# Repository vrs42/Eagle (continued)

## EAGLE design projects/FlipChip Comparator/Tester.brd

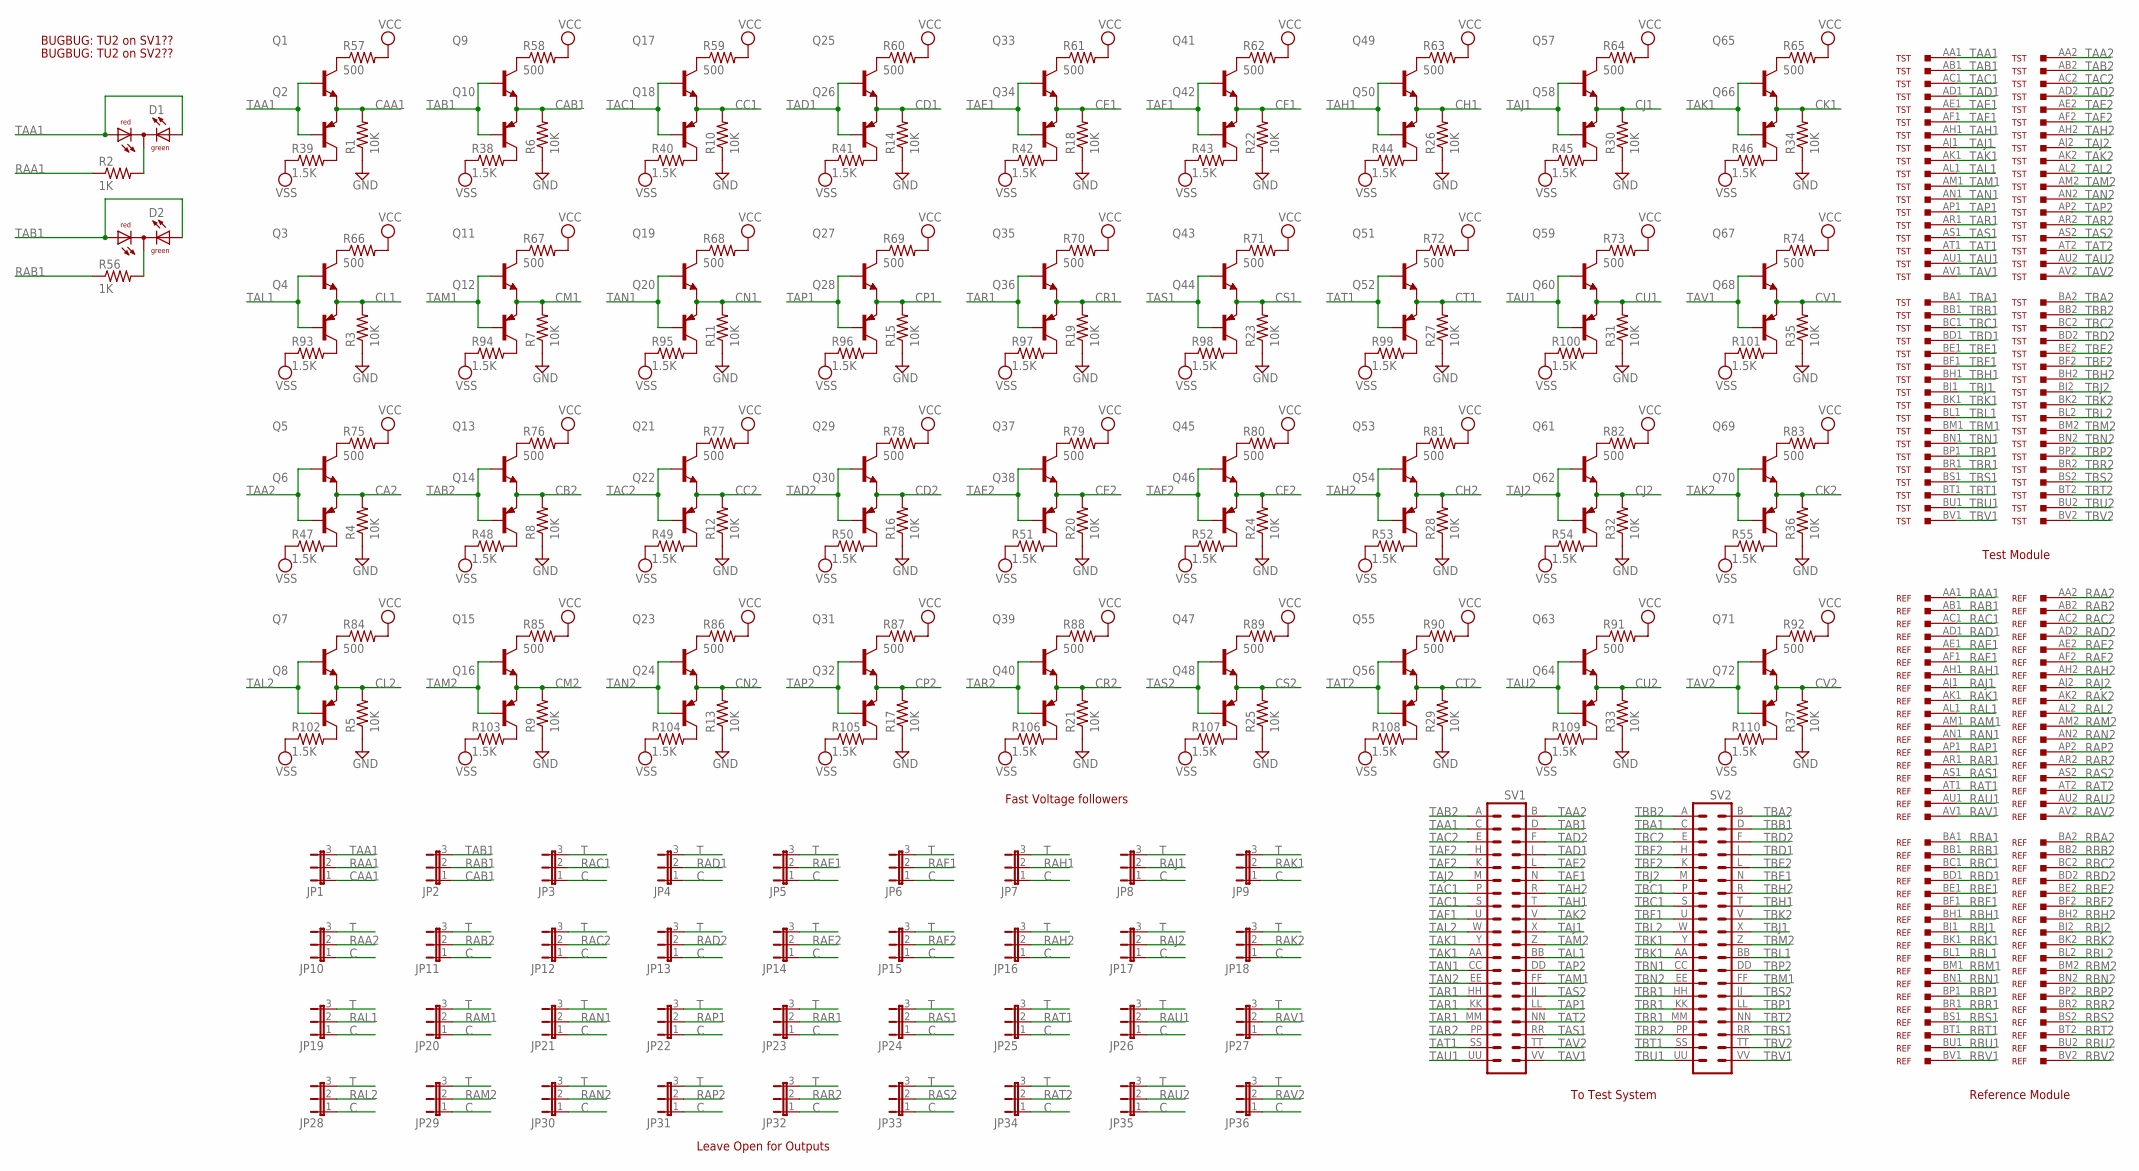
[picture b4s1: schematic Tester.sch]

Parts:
D1, D2: DUOLED5MM
JP1, JP2, JP3, JP4, JP5, JP6, JP7, JP8, JP9, JP10, JP11, JP12, JP13, JP14, JP15, JP16, JP17, JP18, JP19, JP20, JP21, JP22, JP23, JP24, JP25, JP26, JP27, JP28, JP29, JP30, JP31, JP32, JP33, JP34, JP35, JP36: JP2E; JP2
Q1, Q3, Q5, Q7, Q9, Q11, Q13, Q15, Q17, Q19, Q21, Q23, Q25, Q27, Q29, Q31, Q33, Q35, Q37, Q39, Q41, Q43, Q45, Q47, Q49, Q51, Q53, Q55, Q57, Q59, Q61, Q63, Q65, Q67, Q69, Q71: -NPN-TO5; TO5
Q2, Q4, Q6, Q8, Q10, Q12, Q14, Q16, Q18, Q20, Q22, Q24, Q26, Q28, Q30, Q32, Q34, Q36, Q38, Q40, Q42, Q44, Q46, Q48, Q50, Q52, Q54, Q56, Q58, Q60, Q62, Q64, Q66, Q68, Q70, Q72: -PNP-TO5; TO5
R1, R3, R4, R5, R6, R7, R8, R9, R10, R11, R12, R13, R14, R15, R16, R17, R18, R19, R20, R21, R22, R23, R24, R25, R26, R27, R28, R29, R30, R31, R32, R33, R34, R35, R36, R37: 10K; 0207/10
R2, R56: 1K; 0207/10
R38, R39, R40, R41, R42, R43, R44, R45, R46, R47, R48, R49, R50, R51, R52, R53, R54, R55, R93, R94, R95, R96, R97, R98, R99, R100, R101, R102, R103, R104, R105, R106, R107, R108, R109, R110: 1.5K; 0207/10
R57, R58, R59, R60, R61, R62, R63, R64, R65, R66, R67, R68, R69, R70, R71, R72, R73, R74, R75, R76, R77, R78, R79, R80, R81, R82, R83, R84, R85, R86, R87, R88, R89, R90, R91, R92: 500; 0207/10
REF: W971; H807-2
SV1, SV2: DEC40PINV
TST: W971; H807-2

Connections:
C: JP3.1, JP4.1, JP5.1, JP6.1, JP7.1, JP8.1, JP9.1, JP10.1, JP11.1, JP12.1, JP13.1, JP14.1, JP15.1, JP16.1, JP17.1, JP18.1, JP19.1, JP20.1, JP21.1, JP22.1, JP23.1, JP24.1, JP25.1, JP26.1, JP27.1, JP28.1, JP29.1, JP30.1, JP31.1, JP32.1, JP33.1, JP34.1, JP35.1, JP36.1
CA2: Q5.1 (E), Q6.1 (E), R4.2
CAA1: JP1.1, Q1.1 (E), Q2.1 (E), R1.2
CAB1: JP2.1, Q9.1 (E), Q10.1 (E), R6.2
CB2: Q13.1 (E), Q14.1 (E), R8.2
CC1: Q17.1 (E), Q18.1 (E), R10.2
CC2: Q21.1 (E), Q22.1 (E), R12.2
CD1: Q25.1 (E), Q26.1 (E), R14.2
CD2: Q29.1 (E), Q30.1 (E), R16.2
CE1: Q33.1 (E), Q34.1 (E), R18.2
CE2: Q37.1 (E), Q38.1 (E), R20.2
CF1: Q41.1 (E), Q42.1 (E), R22.2
CF2: Q45.1 (E), Q46.1 (E), R24.2
CH1: Q49.1 (E), Q50.1 (E), R26.2
CH2: Q53.1 (E), Q54.1 (E), R28.2
CJ1: Q57.1 (E), Q58.1 (E), R30.2
CJ2: Q61.1 (E), Q62.1 (E), R32.2
CK1: Q65.1 (E), Q66.1 (E), R34.2
CK2: Q69.1 (E), Q70.1 (E), R36.2
CL1: Q3.1 (E), Q4.1 (E), R3.2
CL2: Q7.1 (E), Q8.1 (E), R5.2
CM1: Q11.1 (E), Q12.1 (E), R7.2
CM2: Q15.1 (E), Q16.1 (E), R9.2
CN1: Q19.1 (E), Q20.1 (E), R11.2
CN2: Q23.1 (E), Q24.1 (E), R13.2
CP1: Q27.1 (E), Q28.1 (E), R15.2
CP2: Q31.1 (E), Q32.1 (E), R17.2
CR1: Q35.1 (E), Q36.1 (E), R19.2
CR2: Q39.1 (E), Q40.1 (E), R21.2
CS1: Q43.1 (E), Q44.1 (E), R23.2
CS2: Q47.1 (E), Q48.1 (E), R25.2
CT1: Q51.1 (E), Q52.1 (E), R27.2
CT2: Q55.1 (E), Q56.1 (E), R29.2
CU1: Q59.1 (E), Q60.1 (E), R31.2
CU2: Q63.1 (E), Q64.1 (E), R33.2
CV1: Q67.1 (E), Q68.1 (E), R35.2
CV2: Q71.1 (E), Q72.1 (E), R37.2
GND: R1.1, R3.1, R4.1, R5.1, R6.1, R7.1, R8.1, R9.1, R10.1, R11.1, R12.1, R13.1, R14.1, R15.1, R16.1, R17.1, R18.1, R19.1, R20.1, R21.1, R22.1, R23.1, R24.1, R25.1, R26.1, R27.1, R28.1, R29.1, R30.1, R31.1, R32.1, R33.1, R34.1, R35.1, R36.1, R37.1
unnamed: D1.K (C), R2.2
unnamed: Q2.3 (C), R39.2
unnamed: Q1.3 (C), R57.1
unnamed: Q9.3 (C), R58.1
unnamed: Q17.3 (C), R59.1
unnamed: Q25.3 (C), R60.1
unnamed: Q33.3 (C), R61.1
unnamed: Q41.3 (C), R62.1
unnamed: Q49.3 (C), R63.1
unnamed: Q57.3 (C), R64.1
unnamed: Q65.3 (C), R65.1
unnamed: Q10.3 (C), R38.2
unnamed: Q18.3 (C), R40.2
unnamed: Q26.3 (C), R41.2
unnamed: Q34.3 (C), R42.2
unnamed: Q42.3 (C), R43.2
unnamed: Q50.3 (C), R44.2
unnamed: Q58.3 (C), R45.2
unnamed: Q66.3 (C), R46.2
unnamed: Q6.3 (C), R47.2
unnamed: Q4.3 (C), R93.2
unnamed: Q12.3 (C), R94.2
unnamed: Q14.3 (C), R48.2
unnamed: Q22.3 (C), R49.2
unnamed: Q20.3 (C), R95.2
unnamed: Q28.3 (C), R96.2
unnamed: Q30.3 (C), R50.2
unnamed: Q38.3 (C), R51.2
unnamed: Q36.3 (C), R97.2
unnamed: Q44.3 (C), R98.2
unnamed: Q46.3 (C), R52.2
unnamed: Q54.3 (C), R53.2
unnamed: Q52.3 (C), R99.2
unnamed: Q60.3 (C), R100.2
unnamed: Q62.3 (C), R54.2
unnamed: Q70.3 (C), R55.2
unnamed: Q68.3 (C), R101.2
unnamed: D2.K (C), R56.2
unnamed: Q8.3 (C), R102.2
unnamed: Q16.3 (C), R103.2
unnamed: Q24.3 (C), R104.2
unnamed: Q32.3 (C), R105.2
unnamed: Q40.3 (C), R106.2
unnamed: Q48.3 (C), R107.2
unnamed: Q56.3 (C), R108.2
unnamed: Q64.3 (C), R109.2
unnamed: Q72.3 (C), R110.2
unnamed: Q3.3 (C), R66.1
unnamed: Q11.3 (C), R67.1
unnamed: Q19.3 (C), R68.1
unnamed: Q27.3 (C), R69.1
unnamed: Q35.3 (C), R70.1
unnamed: Q43.3 (C), R71.1
unnamed: Q51.3 (C), R72.1
unnamed: Q59.3 (C), R73.1
unnamed: Q67.3 (C), R74.1
unnamed: Q5.3 (C), R75.1
unnamed: Q13.3 (C), R76.1
unnamed: Q21.3 (C), R77.1
unnamed: Q29.3 (C), R78.1
unnamed: Q37.3 (C), R79.1
unnamed: Q45.3 (C), R80.1
unnamed: Q53.3 (C), R81.1
unnamed: Q61.3 (C), R82.1
unnamed: Q69.3 (C), R83.1
unnamed: Q7.3 (C), R84.1
unnamed: Q15.3 (C), R85.1
unnamed: Q23.3 (C), R86.1
unnamed: Q31.3 (C), R87.1
unnamed: Q39.3 (C), R88.1
unnamed: Q47.3 (C), R89.1
unnamed: Q55.3 (C), R90.1
unnamed: Q63.3 (C), R91.1
unnamed: Q71.3 (C), R92.1
RAA1: JP1.2, R2.1, REF.AA1
RAA2: JP10.2, REF.AA2
RAB1: JP2.2, R56.1, REF.AB1
RAB2: JP11.2, REF.AB2
RAC1: JP3.2, REF.AC1
RAC2: JP12.2, REF.AC2
RAD1: JP4.2, REF.AD1
RAD2: JP13.2, REF.AD2
RAE1: JP5.2, REF.AE1
RAE2: JP14.2, REF.AE2
RAF1: JP6.2, REF.AF1
RAF2: JP15.2, REF.AF2
RAH1: JP7.2, REF.AH1
RAH2: JP16.2, REF.AH2
RAJ1: JP8.2, REF.AJ1
RAJ2: JP17.2, REF.AJ2
RAK1: JP9.2, REF.AK1
RAK2: JP18.2, REF.AK2
RAL1: JP19.2, REF.AL1
RAL2: JP28.2, REF.AL2
RAM1: JP20.2, REF.AM1
RAM2: JP29.2, REF.AM2
RAN1: JP21.2, REF.AN1
RAN2: JP30.2, REF.AN2
RAP1: JP22.2, REF.AP1
RAP2: JP31.2, REF.AP2
RAR1: JP23.2, REF.AR1
RAR2: JP32.2, REF.AR2
RAS1: JP24.2, REF.AS1
RAS2: JP33.2, REF.AS2
RAT1: JP25.2, REF.AT1
RAT2: JP34.2, REF.AT2
RAU1: JP26.2, REF.AU1
RAU2: JP35.2, REF.AU2
RAV1: JP27.2, REF.AV1
RAV2: JP36.2, REF.AV2
RBA1: REF.BA1
RBA2: REF.BA2
RBB1: REF.BB1
RBB2: REF.BB2
RBC1: REF.BC1
RBC2: REF.BC2
RBD1: REF.BD1
RBD2: REF.BD2
RBE1: REF.BE1
RBE2: REF.BE2
RBF1: REF.BF1
RBF2: REF.BF2
RBH1: REF.BH1
RBH2: REF.BH2
RBJ1: REF.BJ1
RBJ2: REF.BJ2
RBK1: REF.BK1
RBK2: REF.BK2
RBL1: REF.BL1
RBL2: REF.BL2
RBM1: REF.BM1
RBM2: REF.BM2
RBN1: REF.BN1
RBN2: REF.BN2
RBP1: REF.BP1
RBP2: REF.BP2
RBR1: REF.BR1
RBR2: REF.BR2
RBS1: REF.BS1
RBS2: REF.BS2
RBT1: REF.BT1
RBT2: REF.BT2
RBU1: REF.BU1
RBU2: REF.BU2
RBV1: REF.BV1
RBV2: REF.BV2
T: JP3.3, JP4.3, JP5.3, JP6.3, JP7.3, JP8.3, JP9.3, JP10.3, JP11.3, JP12.3, JP13.3, JP14.3, JP15.3, JP16.3, JP17.3, JP18.3, JP19.3, JP20.3, JP21.3, JP22.3, JP23.3, JP24.3, JP25.3, JP26.3, JP27.3, JP28.3, JP29.3, JP30.3, JP31.3, JP32.3, JP33.3, JP34.3, JP35.3, JP36.3
TAA1: D1.AG, D1.AR, JP1.3, Q1.2 (B), Q2.2 (B), SV1.C (3), TST.AA1
TAA2: Q5.2 (B), Q6.2 (B), SV1.B (2), TST.AA2
TAB1: D2.AG, D2.AR, JP2.3, Q9.2 (B), Q10.2 (B), SV1.D (4), TST.AB1
TAB2: Q13.2 (B), Q14.2 (B), SV1.A (1), TST.AB2
TAC1: Q17.2 (B), Q18.2 (B), SV1.P (13), SV1.S (15), TST.AC1
TAC2: Q21.2 (B), Q22.2 (B), SV1.E (5), TST.AC2
TAD1: Q25.2 (B), Q26.2 (B), SV1.J (8), TST.AD1
TAD2: Q29.2 (B), Q30.2 (B), SV1.F (6), TST.AD2
TAE1: Q33.2 (B), Q34.2 (B), SV1.N (12), TST.AE1
TAE2: Q37.2 (B), Q38.2 (B), SV1.L (10), TST.AE2
TAF1: Q41.2 (B), Q42.2 (B), SV1.U (17), TST.AF1
TAF2: Q45.2 (B), Q46.2 (B), SV1.H (7), SV1.K (9), TST.AF2
TAH1: Q49.2 (B), Q50.2 (B), SV1.T (16), TST.AH1
TAH2: Q53.2 (B), Q54.2 (B), SV1.R (14), TST.AH2
TAJ1: Q57.2 (B), Q58.2 (B), SV1.X (20), TST.AJ1
TAJ2: Q61.2 (B), Q62.2 (B), SV1.M (11), TST.AJ2
TAK1: Q65.2 (B), Q66.2 (B), SV1.AA (23), SV1.Y (21), TST.AK1
TAK2: Q69.2 (B), Q70.2 (B), SV1.V (18), TST.AK2
TAL1: Q3.2 (B), Q4.2 (B), SV1.BB (24), TST.AL1
TAL2: Q7.2 (B), Q8.2 (B), SV1.W (19), TST.AL2
TAM1: Q11.2 (B), Q12.2 (B), SV1.FF (28), TST.AM1
TAM2: Q15.2 (B), Q16.2 (B), SV1.Z (22), TST.AM2
TAN1: Q19.2 (B), Q20.2 (B), SV1.CC (25), TST.AN1
TAN2: Q23.2 (B), Q24.2 (B), SV1.EE (27), TST.AN2
TAP1: Q27.2 (B), Q28.2 (B), SV1.LL (32), TST.AP1
TAP2: Q31.2 (B), Q32.2 (B), SV1.DD (26), TST.AP2
TAR1: Q35.2 (B), Q36.2 (B), SV1.HH (29), SV1.KK (31), SV1.MM (33), TST.AR1
TAR2: Q39.2 (B), Q40.2 (B), SV1.PP (35), TST.AR2
TAS1: Q43.2 (B), Q44.2 (B), SV1.RR (36), TST.AS1
TAS2: Q47.2 (B), Q48.2 (B), SV1.JJ (30), TST.AS2
TAT1: Q51.2 (B), Q52.2 (B), SV1.SS (37), TST.AT1
TAT2: Q55.2 (B), Q56.2 (B), SV1.NN (34), TST.AT2
TAU1: Q59.2 (B), Q60.2 (B), SV1.UU (39), TST.AU1
TAU2: Q63.2 (B), Q64.2 (B), TST.AU2
TAV1: Q67.2 (B), Q68.2 (B), SV1.VV (40), TST.AV1
TAV2: Q71.2 (B), Q72.2 (B), SV1.TT (38), TST.AV2
TBA1: SV2.C (3), TST.BA1
TBA2: SV2.B (2), TST.BA2
TBB1: SV2.D (4), TST.BB1
TBB2: SV2.A (1), TST.BB2
TBC1: SV2.P (13), SV2.S (15), TST.BC1
TBC2: SV2.E (5), TST.BC2
TBD1: SV2.J (8), TST.BD1
TBD2: SV2.F (6), TST.BD2
TBE1: SV2.N (12), TST.BE1
TBE2: SV2.L (10), TST.BE2
TBF1: SV2.U (17), TST.BF1
TBF2: SV2.H (7), SV2.K (9), TST.BF2
TBH1: SV2.T (16), TST.BH1
TBH2: SV2.R (14), TST.BH2
TBJ1: SV2.X (20), TST.BJ1
TBJ2: SV2.M (11), TST.BJ2
TBK1: SV2.AA (23), SV2.Y (21), TST.BK1
TBK2: SV2.V (18), TST.BK2
TBL1: SV2.BB (24), TST.BL1
TBL2: SV2.W (19), TST.BL2
TBM1: SV2.FF (28), TST.BM1
TBM2: SV2.Z (22), TST.BM2
TBN1: SV2.CC (25), TST.BN1
TBN2: SV2.EE (27), TST.BN2
TBP1: SV2.LL (32), TST.BP1
TBP2: SV2.DD (26), TST.BP2
TBR1: SV2.HH (29), SV2.KK (31), SV2.MM (33), TST.BR1
TBR2: SV2.PP (35), TST.BR2
TBS1: SV2.RR (36), TST.BS1
TBS2: SV2.JJ (30), TST.BS2
TBT1: SV2.SS (37), TST.BT1
TBT2: SV2.NN (34), TST.BT2
TBU1: SV2.UU (39), TST.BU1
TBU2: TST.BU2
TBV1: SV2.VV (40), TST.BV1
TBV2: SV2.TT (38), TST.BV2
VCC: R57.2, R58.2, R59.2, R60.2, R61.2, R62.2, R63.2, R64.2, R65.2, R66.2, R67.2, R68.2, R69.2, R70.2, R71.2, R72.2, R73.2, R74.2, R75.2, R76.2, R77.2, R78.2, R79.2, R80.2, R81.2, R82.2, R83.2, R84.2, R85.2, R86.2, R87.2, R88.2, R89.2, R90.2, R91.2, R92.2
VSS: R38.1, R39.1, R40.1, R41.1, R42.1, R43.1, R44.1, R45.1, R46.1, R47.1, R48.1, R49.1, R50.1, R51.1, R52.1, R53.1, R54.1, R55.1, R93.1, R94.1, R95.1, R96.1, R97.1, R98.1, R99.1, R100.1, R101.1, R102.1, R103.1, R104.1, R105.1, R106.1, R107.1, R108.1, R109.1, R110.1

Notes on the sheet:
BUGBUG: TU2 on SV1??
Fast Voltage followers
Leave Open for Outputs
Test Module
Reference Module
To Test System
BUGBUG: TU2 on SV2??

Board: 2 copper layers, 224 parts (0 on the bottom side), 222 nets, no tracks yet.
